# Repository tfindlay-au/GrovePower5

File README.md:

# Grove Power 5

### Overview
This project provides a schematic to build a 5v power source for Grove devices.

The input will be a common USB-C plug.

Further this project now includes a UART interface via an FTDI 201 chip which provides a serial interface to the grove device.

### Requirements
This project was built using Kicad 5.1.10

### Outputs
- Gerber file
- Bill of materials file

### Costs
Estimated Costs
- 19 components
- PCB
- Labor and solder for SMD components
- PLA case

### Changes
- v0.2: Second release
  - Reduced the size of the board, removed locating holes
  - Renamed to Grove Power 5
- v0.1: First release
  - Minor fix to footprint for L1

### Future ideas
- Add LED power indicator
- Add On/Off switch

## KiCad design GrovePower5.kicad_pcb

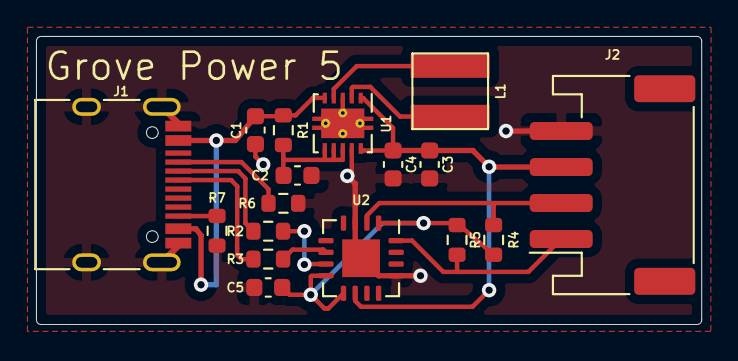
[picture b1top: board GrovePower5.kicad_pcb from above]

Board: 2 copper layers, 37.0 x 16.0 mm, 17 parts (0 on the bottom side), 15 nets.

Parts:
C1, C3, C4: 10uF; C_0603_1608Metric
C2, C5: 0.1uF; C_0603_1608Metric
J1: USB_C_Receptacle_USB2.0; USB_C_Receptacle_HRO_TYPE-C-31-M-12
J2: 114020164; JST_PH_S4B-PH-SM4-TB_1x04-1MP_P2.00mm_Horizontal
L1: 2.2uH; L_TDK_VLS4012
R1: 100 Ohm; R_0603_1608Metric
R2, R3: 27R; R_0603_1608Metric
R4, R5: 1k Ohm; R_0603_1608Metric
R6, R7: 5.1k Ohm; R_0603_1608Metric
U1: TPS63002; Texas_DRC0010J_ThermalVias
U2: FT201XQ; QFN-16-1EP_4x4mm_P0.65mm_EP2.1x2.1mm

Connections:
+3V3: C5.1, R4.1, R5.1, U2.1, U2.8, U2.9
+5V: C3.1, C4.1, J2.3, U1.1, U1.10, U2.10
/SCL: J2.1, R4.2, U2.16
/SDA: J2.2, R5.2, U2.2
/USBDM: J1.B7, R2.2
/USBDP: J1.A6, R3.2
GND: C1.2, C2.2, C3.2, C4.2, C5.2, J1.A1, J1.A12, J1.B1, J1.B12, J1.S1, J2.4, R6.2, R7.2, U1.3, U1.9, U1.11, U2.3, U2.13, U2.17
unnamed: C2.1, R1.2, U1.6, U1.7, U1.8
unnamed: J1.A5, R6.1
unnamed: J1.B5, R7.1
unnamed: L1.1, U1.4
unnamed: L1.2, U1.2
unnamed: R2.1, U2.7
unnamed: R3.1, U2.6
VBUS: C1.1, J1.A4, J1.A9, J1.B4, J1.B9, R1.1, U1.5

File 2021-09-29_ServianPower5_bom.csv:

Comment,Designator,Footprint,LCSC
"10uF","C1,C3,C4","Capacitor_SMD:C_0603_1608Metric","C599662"
"0.1uF","C2,C5","Capacitor_SMD:C_0603_1608Metric","C2169243"
"USB_C_Receptacle_USB2.0","J1","Connector_USB:USB_C_Receptacle_HRO_TYPE-C-31-M-12","C165948"
"114020164","J2","Connector_JST:JST_PH_S4B-PH-SM4-TB_1x04-1MP_P2.00mm_Horizontal","C604849"
"2.2uH","L1","Inductor_SMD:L_6.3x6.3_H3","C2047713"
"100 Ohm","R1","Resistor_SMD:R_0603_1608Metric","C105588"
"27R","R2,R3","Resistor_SMD:R_0603_1608Metric","C137753"
"1k Ohm","R4,R5","Resistor_SMD:R_0603_1608Metric","C22548"
"5.1k Ohm","R6,R7","Resistor_SMD:R_0603_1608Metric","C105580"
"TPS63002","U1","Package_SON:Texas_DRC0010J_ThermalVias","C116655"
"FT201XQ","U2","Package_DFN_QFN:QFN-16-1EP_4x4mm_P0.65mm_EP2.1x2.1mm","C2651887"

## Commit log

2021-09-21 Updated with component details
2021-09-29 Updated with component details for JLPCB
2021-10-10 Final submission to JLPCB with LCSC part numbers
2021-11-03 Updated footprint for L1
2021-11-03 Added images, updated README and reduced the board size
2021-11-09 Rename the project to avoid trademark issues
